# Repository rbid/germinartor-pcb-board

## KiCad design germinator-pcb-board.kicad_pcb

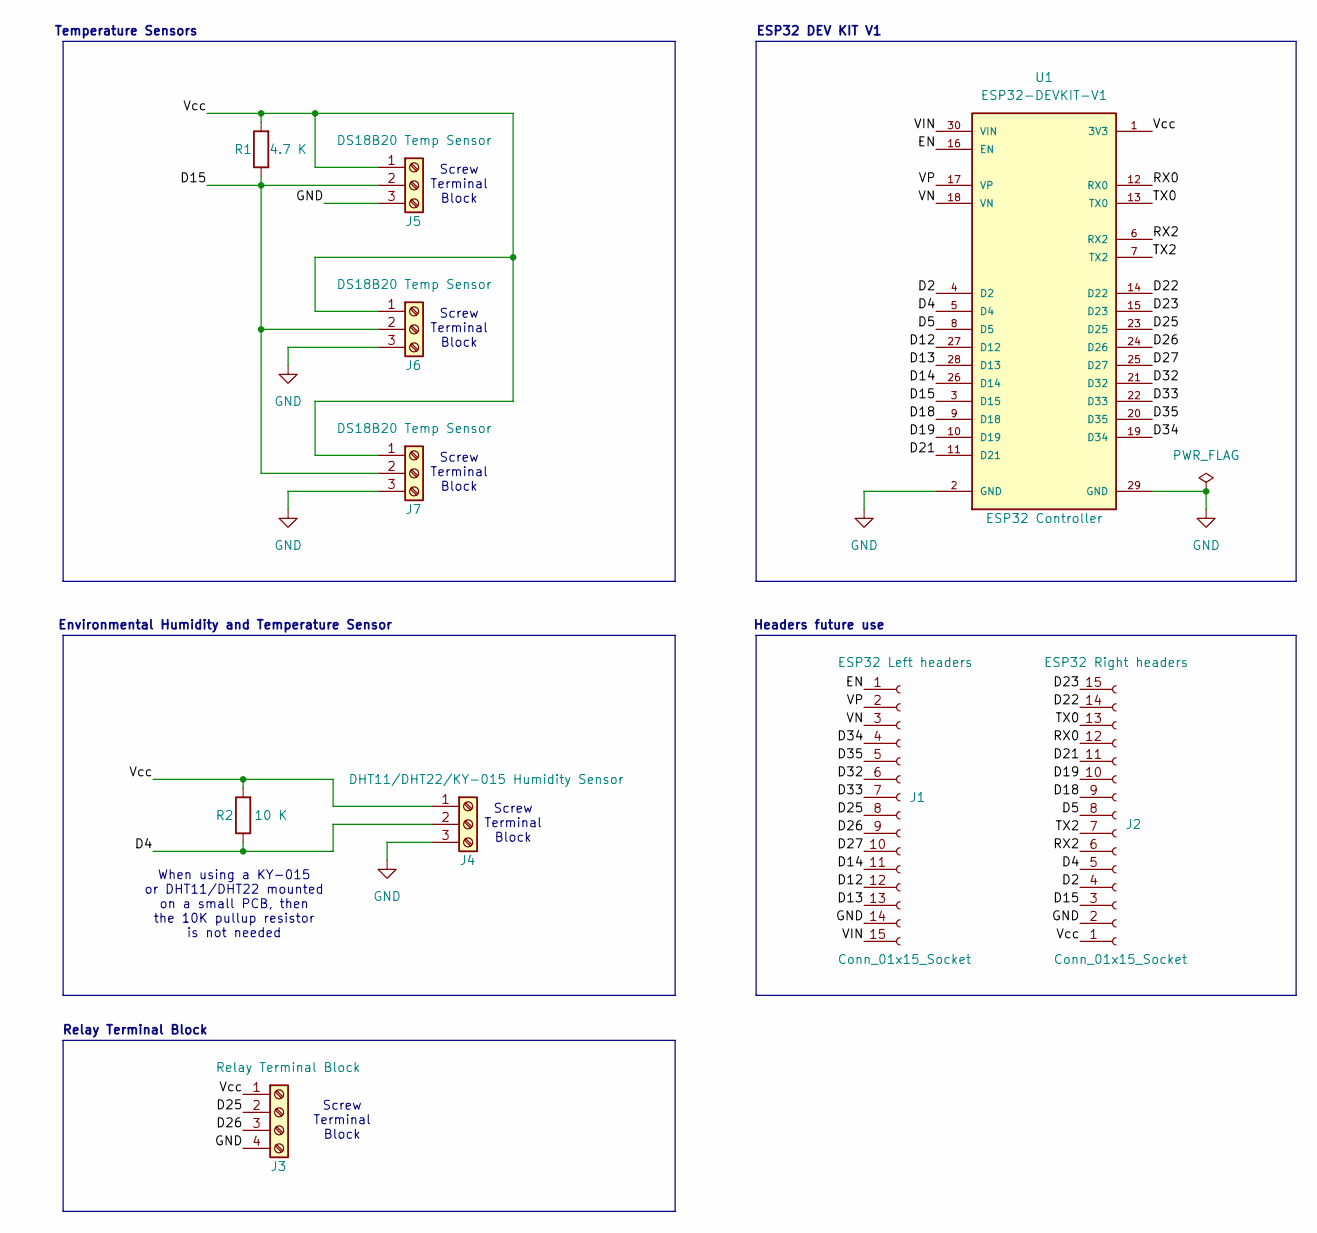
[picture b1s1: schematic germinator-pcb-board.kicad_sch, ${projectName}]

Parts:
J1, J2: Conn_01x15_Socket; PinSocket_1x15_P2.54mm_Vertical
J3: Screw_Terminal_01x04; TerminalBlock_MaiXu_MX126-5.0-04P_1x04_P5.00mm
J4, J5, J6, J7: Screw_Terminal_01x03; TerminalBlock_MaiXu_MX126-5.0-03P_1x03_P5.00mm
R1: 4.7 K; R_Axial_DIN0207_L6.3mm_D2.5mm_P7.62mm_Horizontal
R2: 10 K; R_Axial_DIN0207_L6.3mm_D2.5mm_P7.62mm_Horizontal
U1: ESP32-DEVKIT-V1; ESP32_DEVKIT_V1

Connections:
/D2: J2.4, U1.4 (D2)
/D4: J2.5, J4.2, R2.1, U1.5 (D4)
/D5: J2.8, U1.8 (D5)
/D12: J1.12, U1.27 (D12)
/D13: J1.13, U1.28 (D13)
/D14: J1.11, U1.26 (D14)
/D15: J2.3, J5.2, J6.2, J7.2, R1.1, U1.3 (D15)
/D18: J2.9, U1.9 (D18)
/D19: J2.10, U1.10 (D19)
/D21: J2.11, U1.11 (D21)
/D22: J2.14, U1.14 (D22)
/D23: J2.15, U1.15 (D23)
/D25: J1.8, J3.2, U1.23 (D25)
/D26: J1.9, J3.3, U1.24 (D26)
/D27: J1.10, U1.25 (D27)
/D32: J1.6, U1.21 (D32)
/D33: J1.7, U1.22 (D33)
/D34: J1.4, U1.19 (D34)
/D35: J1.5, U1.20 (D35)
/EN: J1.1, U1.16 (EN)
/RX0: J2.12, U1.12 (RX0)
/RX2: J2.6, U1.6 (RX2)
/TX0: J2.13, U1.13 (TX0)
/TX2: J2.7, U1.7 (TX2)
/VIN: J1.15, U1.30 (VIN)
/VN: J1.3, U1.18 (VN)
/VP: J1.2, U1.17 (VP)
/Vcc: J2.1, J3.1, J4.1, J5.1, J6.1, J7.1, R1.2, R2.2, U1.1 (3V3)
GND: J1.14, J2.2, J3.4, J4.3, J5.3, J6.3, J7.3, U1.2 (GND), U1.29 (GND)

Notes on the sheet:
Screw Terminal Block
Headers future use
Environmental Humidity and Temperature Sensor
Temperature Sensors
When using a KY-015 or DHT11/DHT22 mounted on a small PCB, then the 10K pullup resistor is not needed
Relay Terminal Block
ESP32 DEV KIT V1

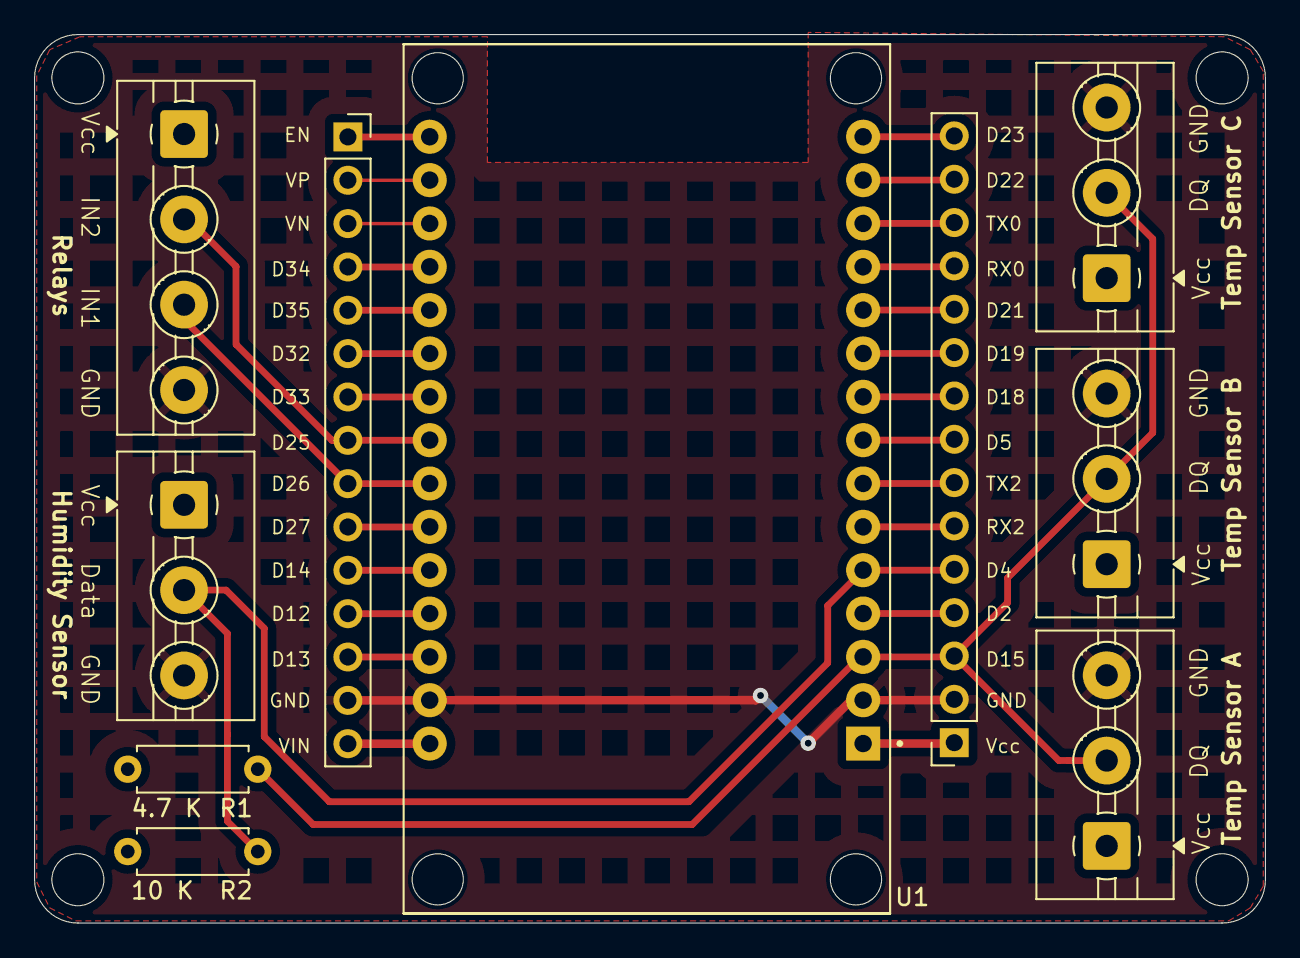
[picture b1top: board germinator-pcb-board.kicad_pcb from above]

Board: 2 copper layers, 72.1 x 52.1 mm, 11 parts (1 on the bottom side), 29 nets.

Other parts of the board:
QR*****: https://github.com/rbid/germinartor-pcb-board; germinartor-pcb-board-qrcode

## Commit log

2025-01-23 Initial clean version
2025-01-24 Schematics step 1: Setup Preferences & Page Settings
2025-01-24 Schematics step 2: symbols added
2025-01-24 Schematics step 3: Arrange and Annotate
2025-01-24 Schematics step 5 & 6: Nets and Electric rules checking
2025-01-24 Schematics step 4: Wiring
2025-01-24 Schematics step 7: Comments
2025-01-24 Layout Step 1: PCB Editor and Page Settings
2025-01-24 Layout Step 2: Outline and Mechanical Constraints
2025-01-24 Layout step 3: Place Footprints
2025-01-24 Layout step 4: Routing
2025-01-24 Fix Footprint for ESP32 that has a miss match
2025-01-27 Layout step 5: Silkscreen
2025-01-27 Layout step 6: Design Rules Check
2025-01-27 Layout step 7: export gerber files
2025-01-27 Create LICENSE
    Adding MIT license.
2025-02-08 changing tracks widht
2025-02-08 adding terminal blocks 3d models and making traces wider
